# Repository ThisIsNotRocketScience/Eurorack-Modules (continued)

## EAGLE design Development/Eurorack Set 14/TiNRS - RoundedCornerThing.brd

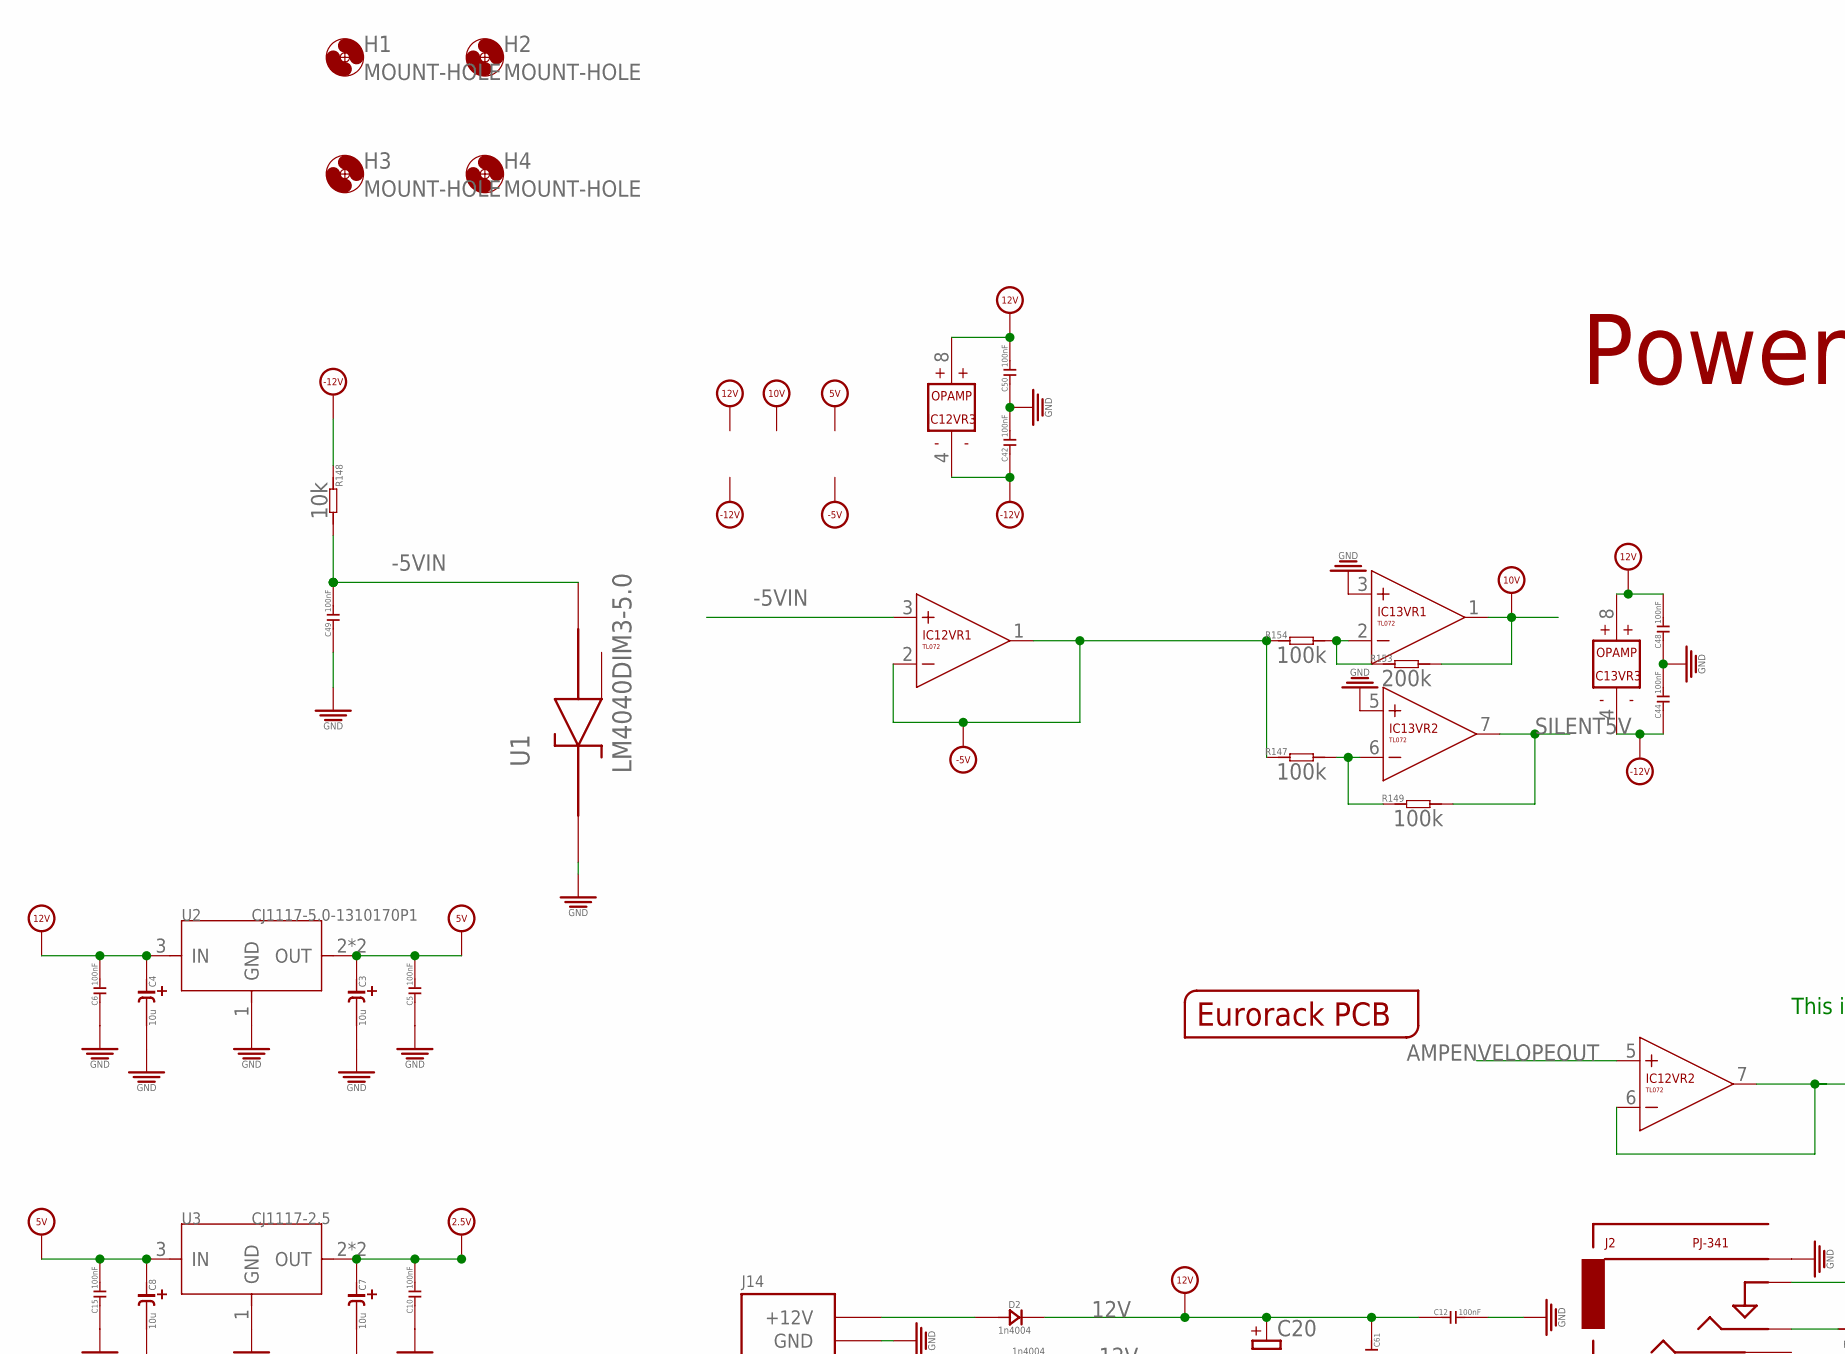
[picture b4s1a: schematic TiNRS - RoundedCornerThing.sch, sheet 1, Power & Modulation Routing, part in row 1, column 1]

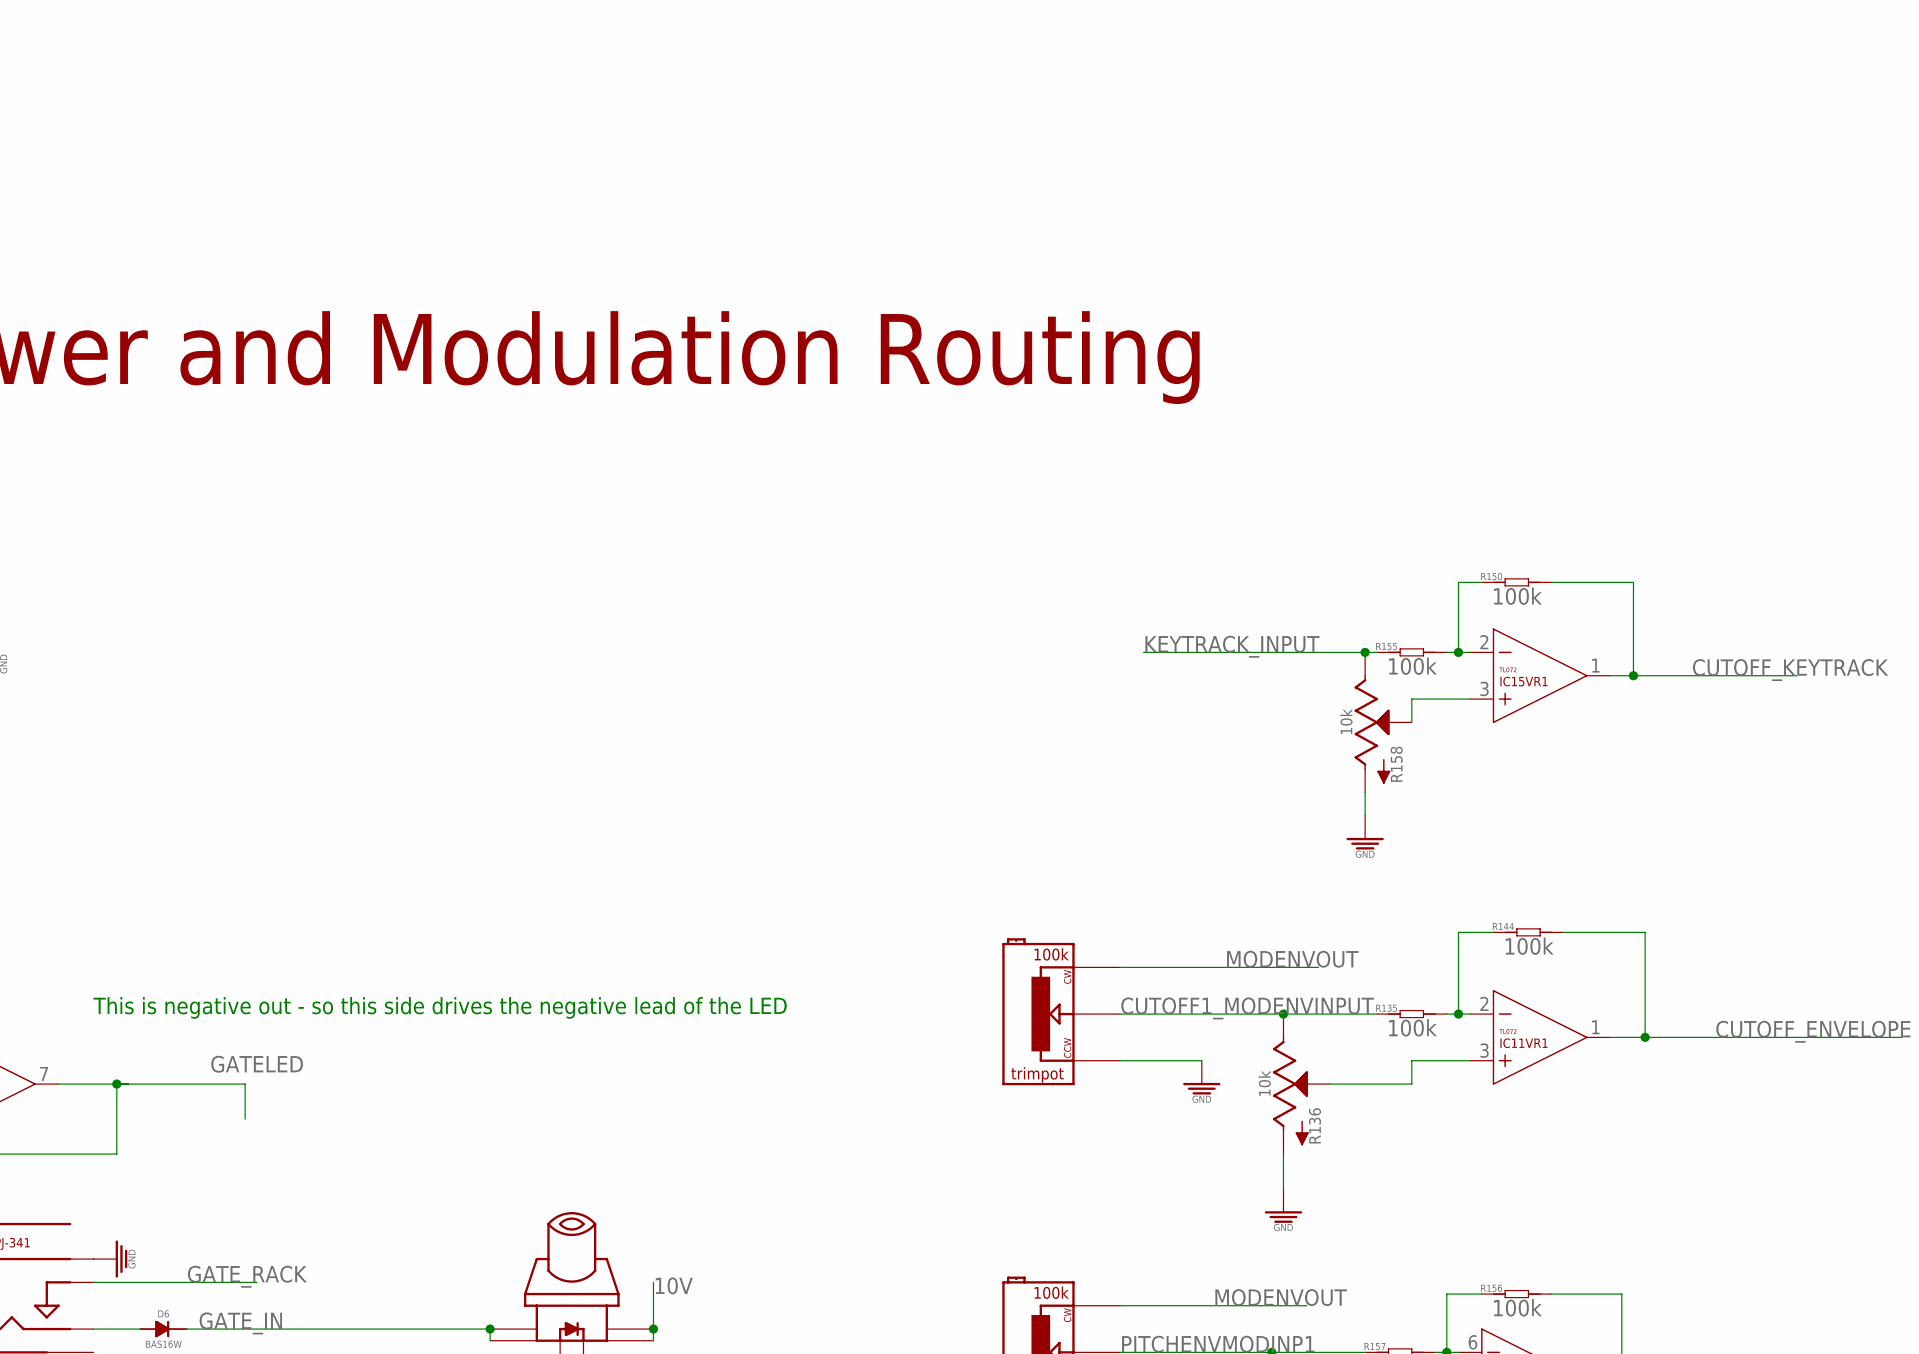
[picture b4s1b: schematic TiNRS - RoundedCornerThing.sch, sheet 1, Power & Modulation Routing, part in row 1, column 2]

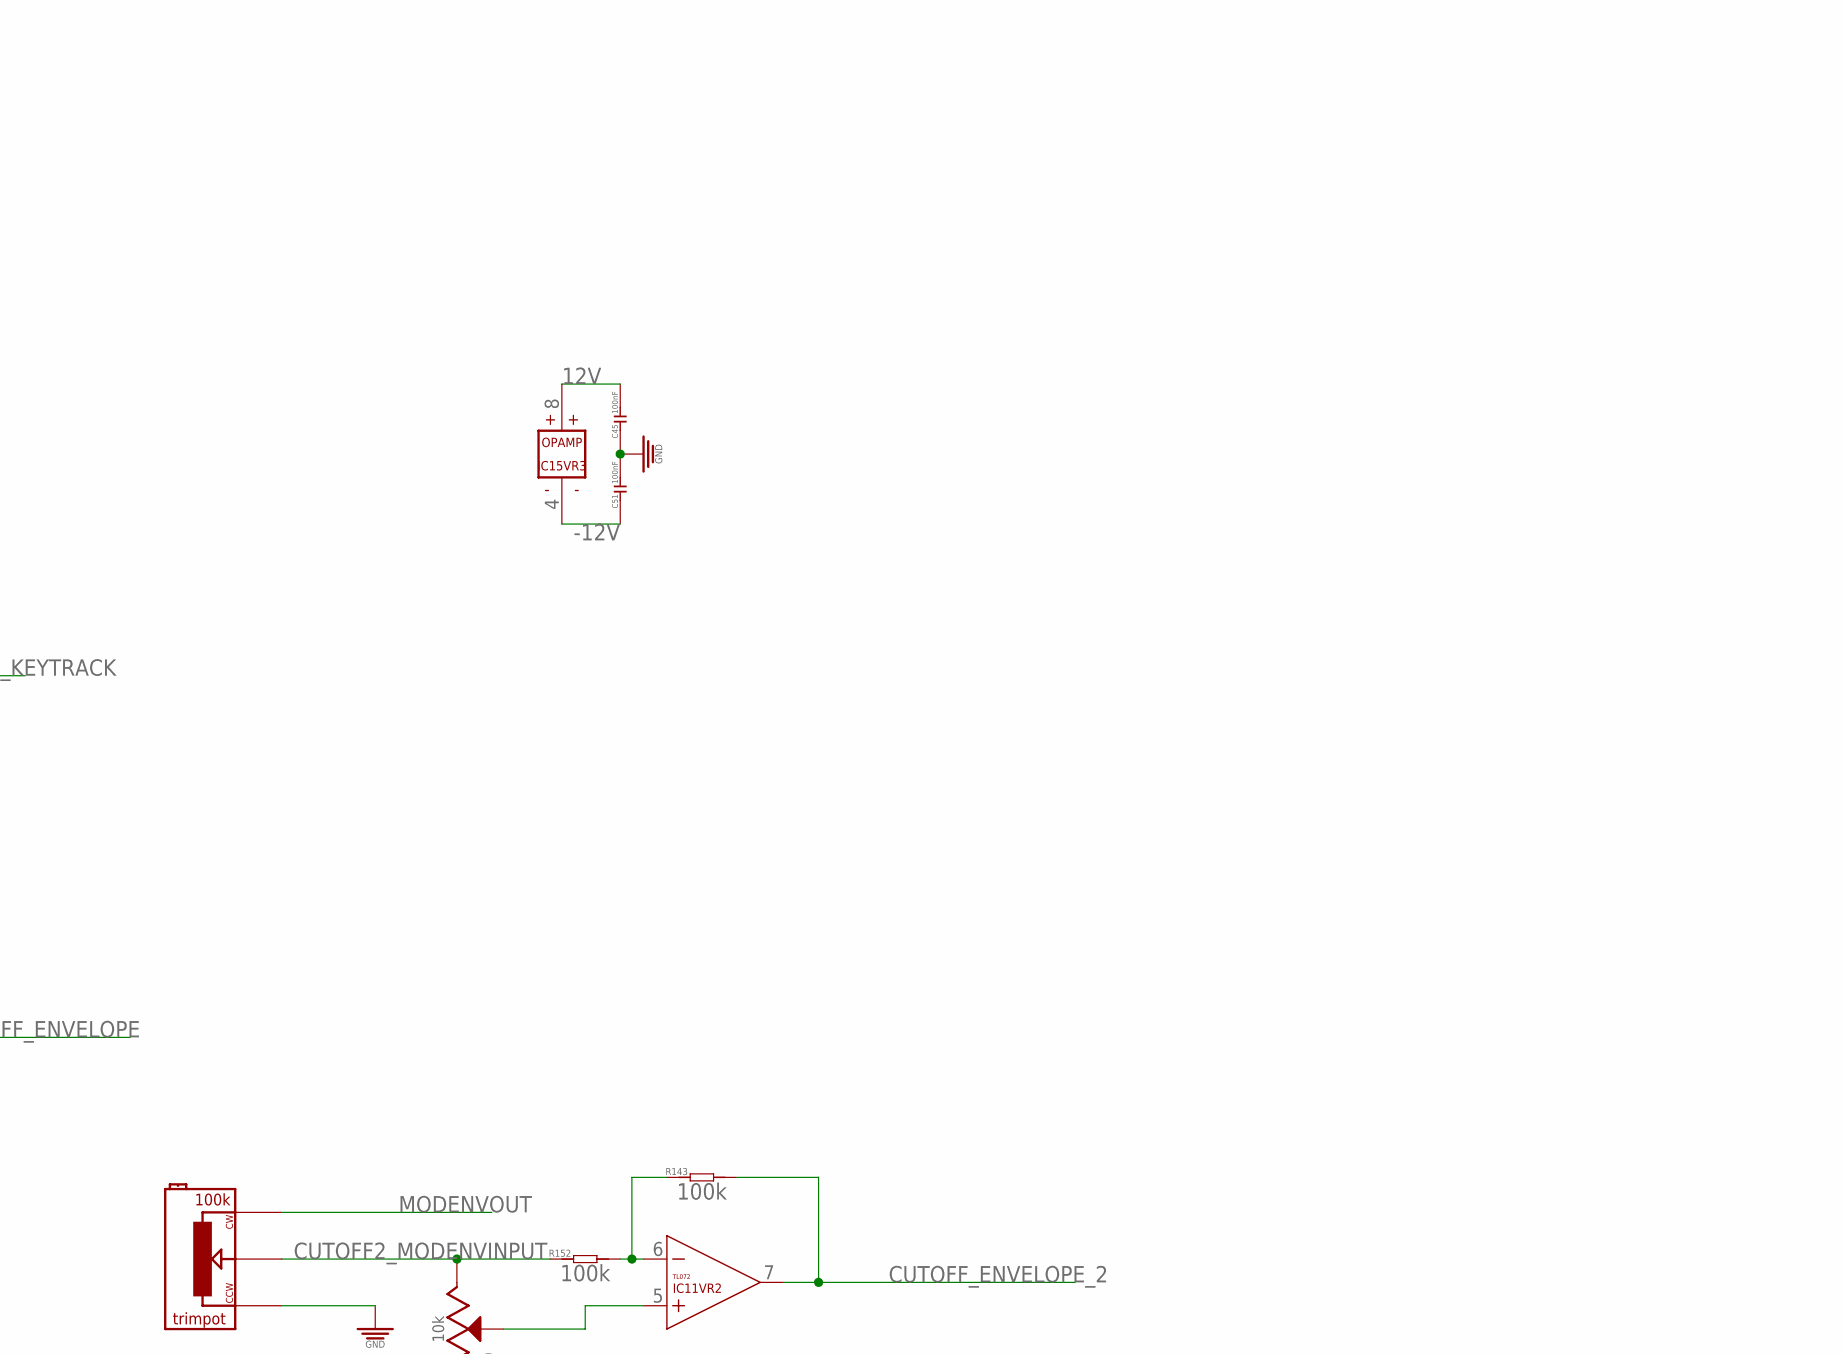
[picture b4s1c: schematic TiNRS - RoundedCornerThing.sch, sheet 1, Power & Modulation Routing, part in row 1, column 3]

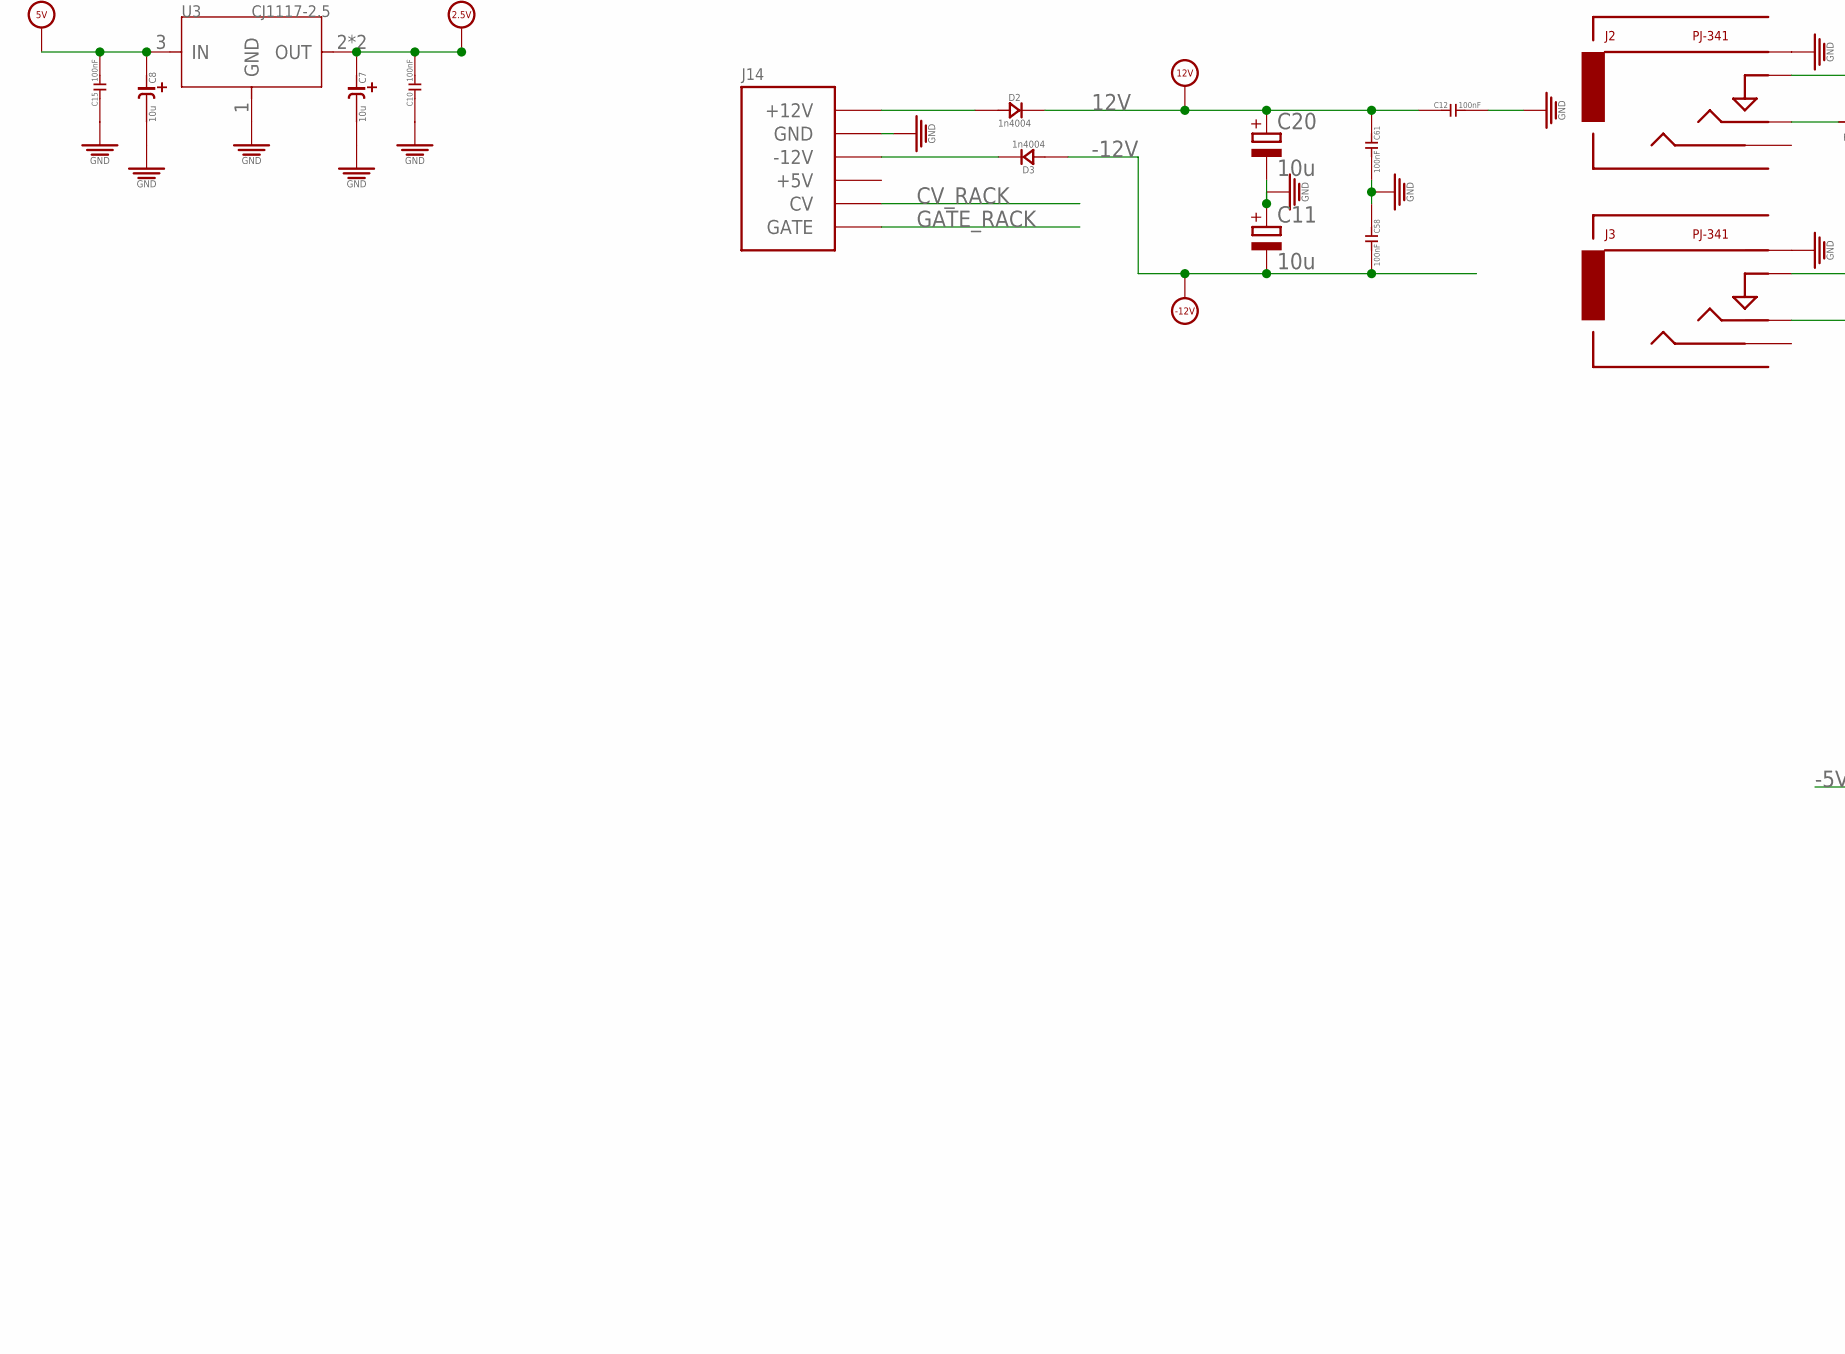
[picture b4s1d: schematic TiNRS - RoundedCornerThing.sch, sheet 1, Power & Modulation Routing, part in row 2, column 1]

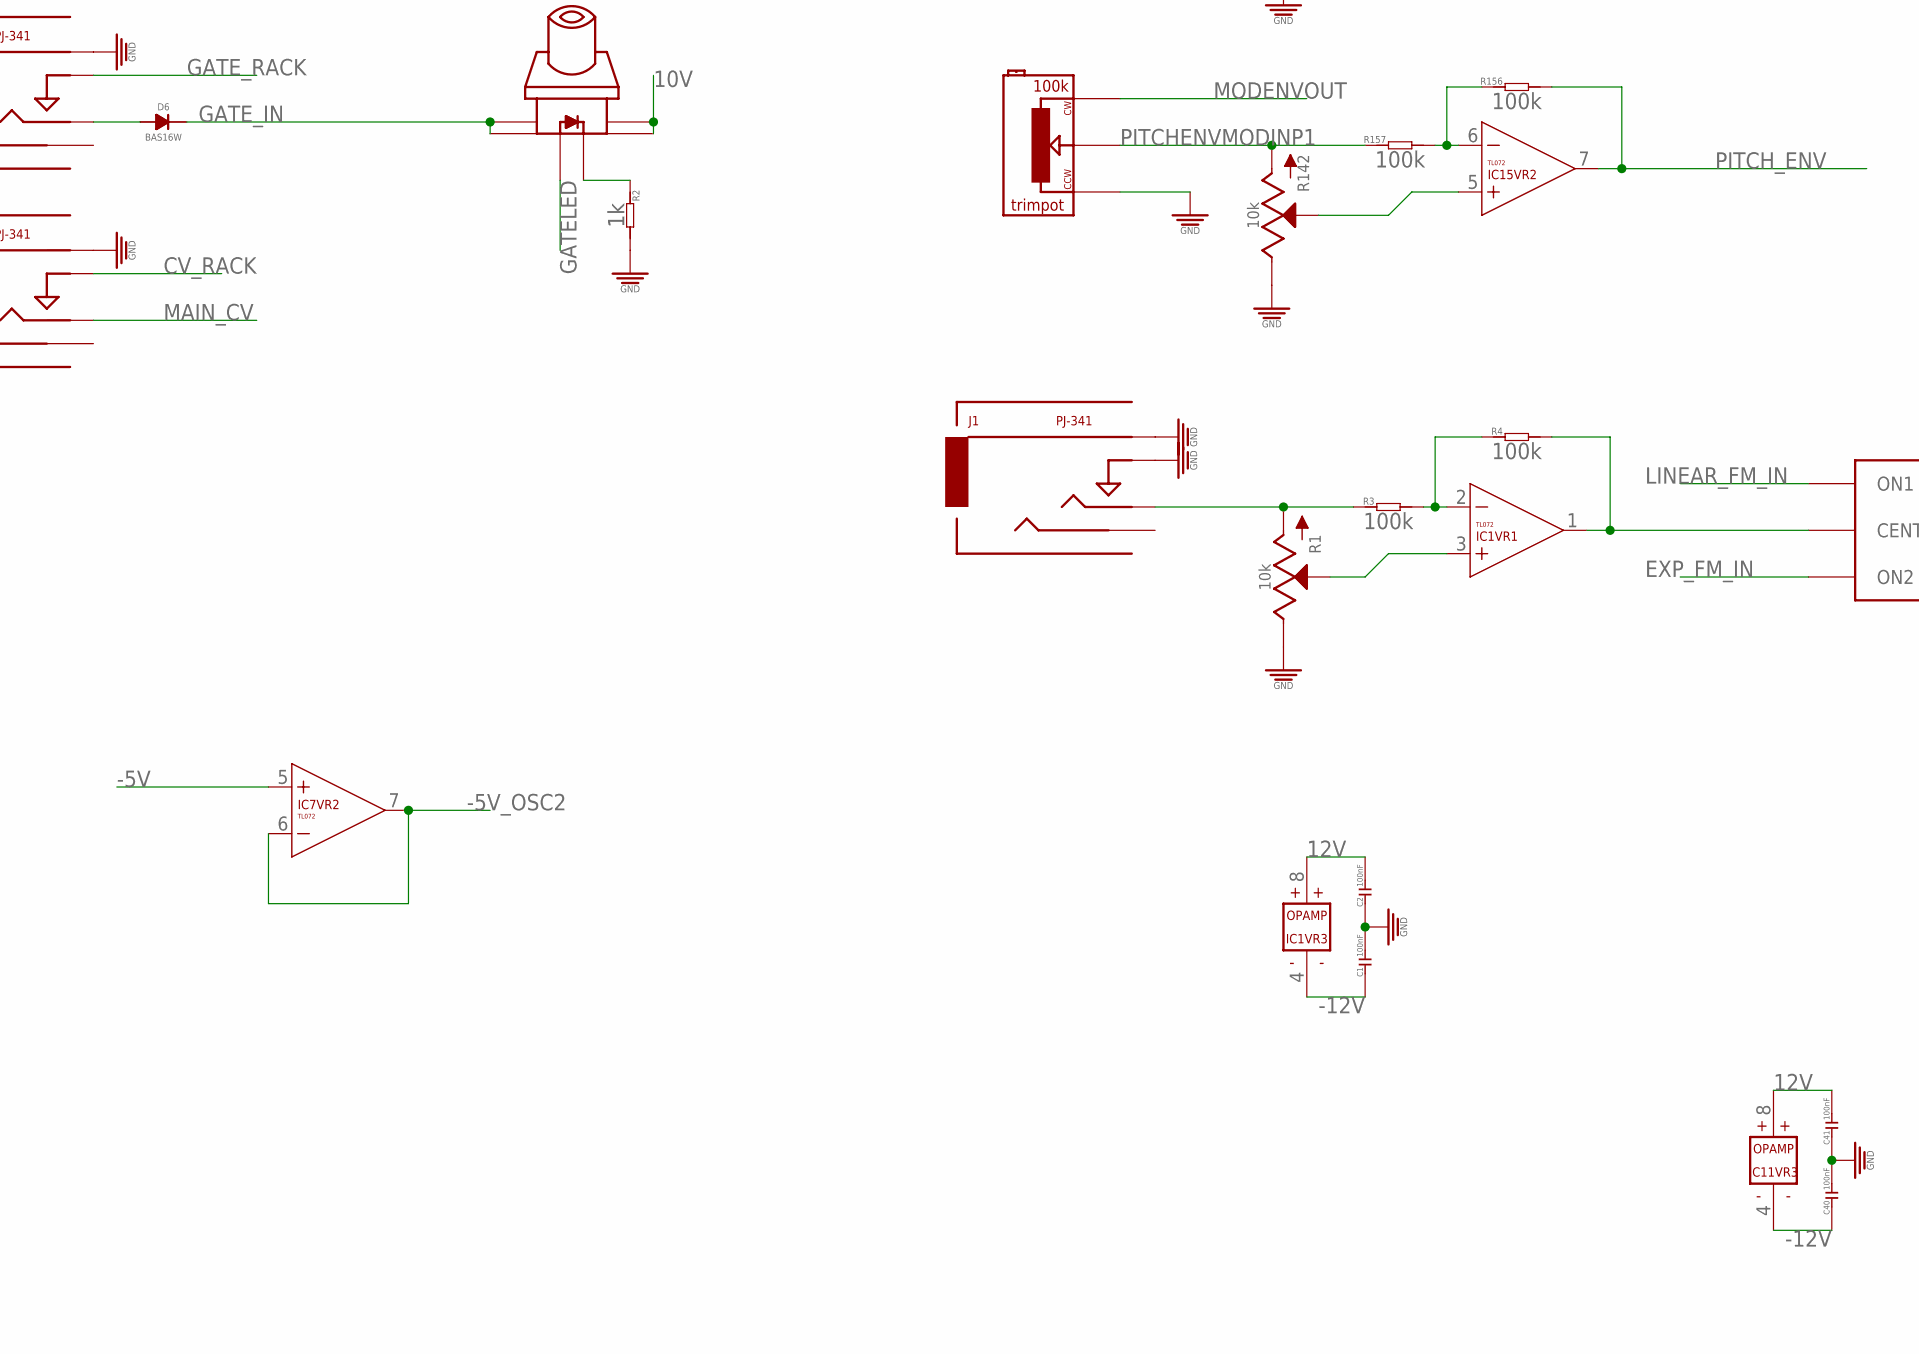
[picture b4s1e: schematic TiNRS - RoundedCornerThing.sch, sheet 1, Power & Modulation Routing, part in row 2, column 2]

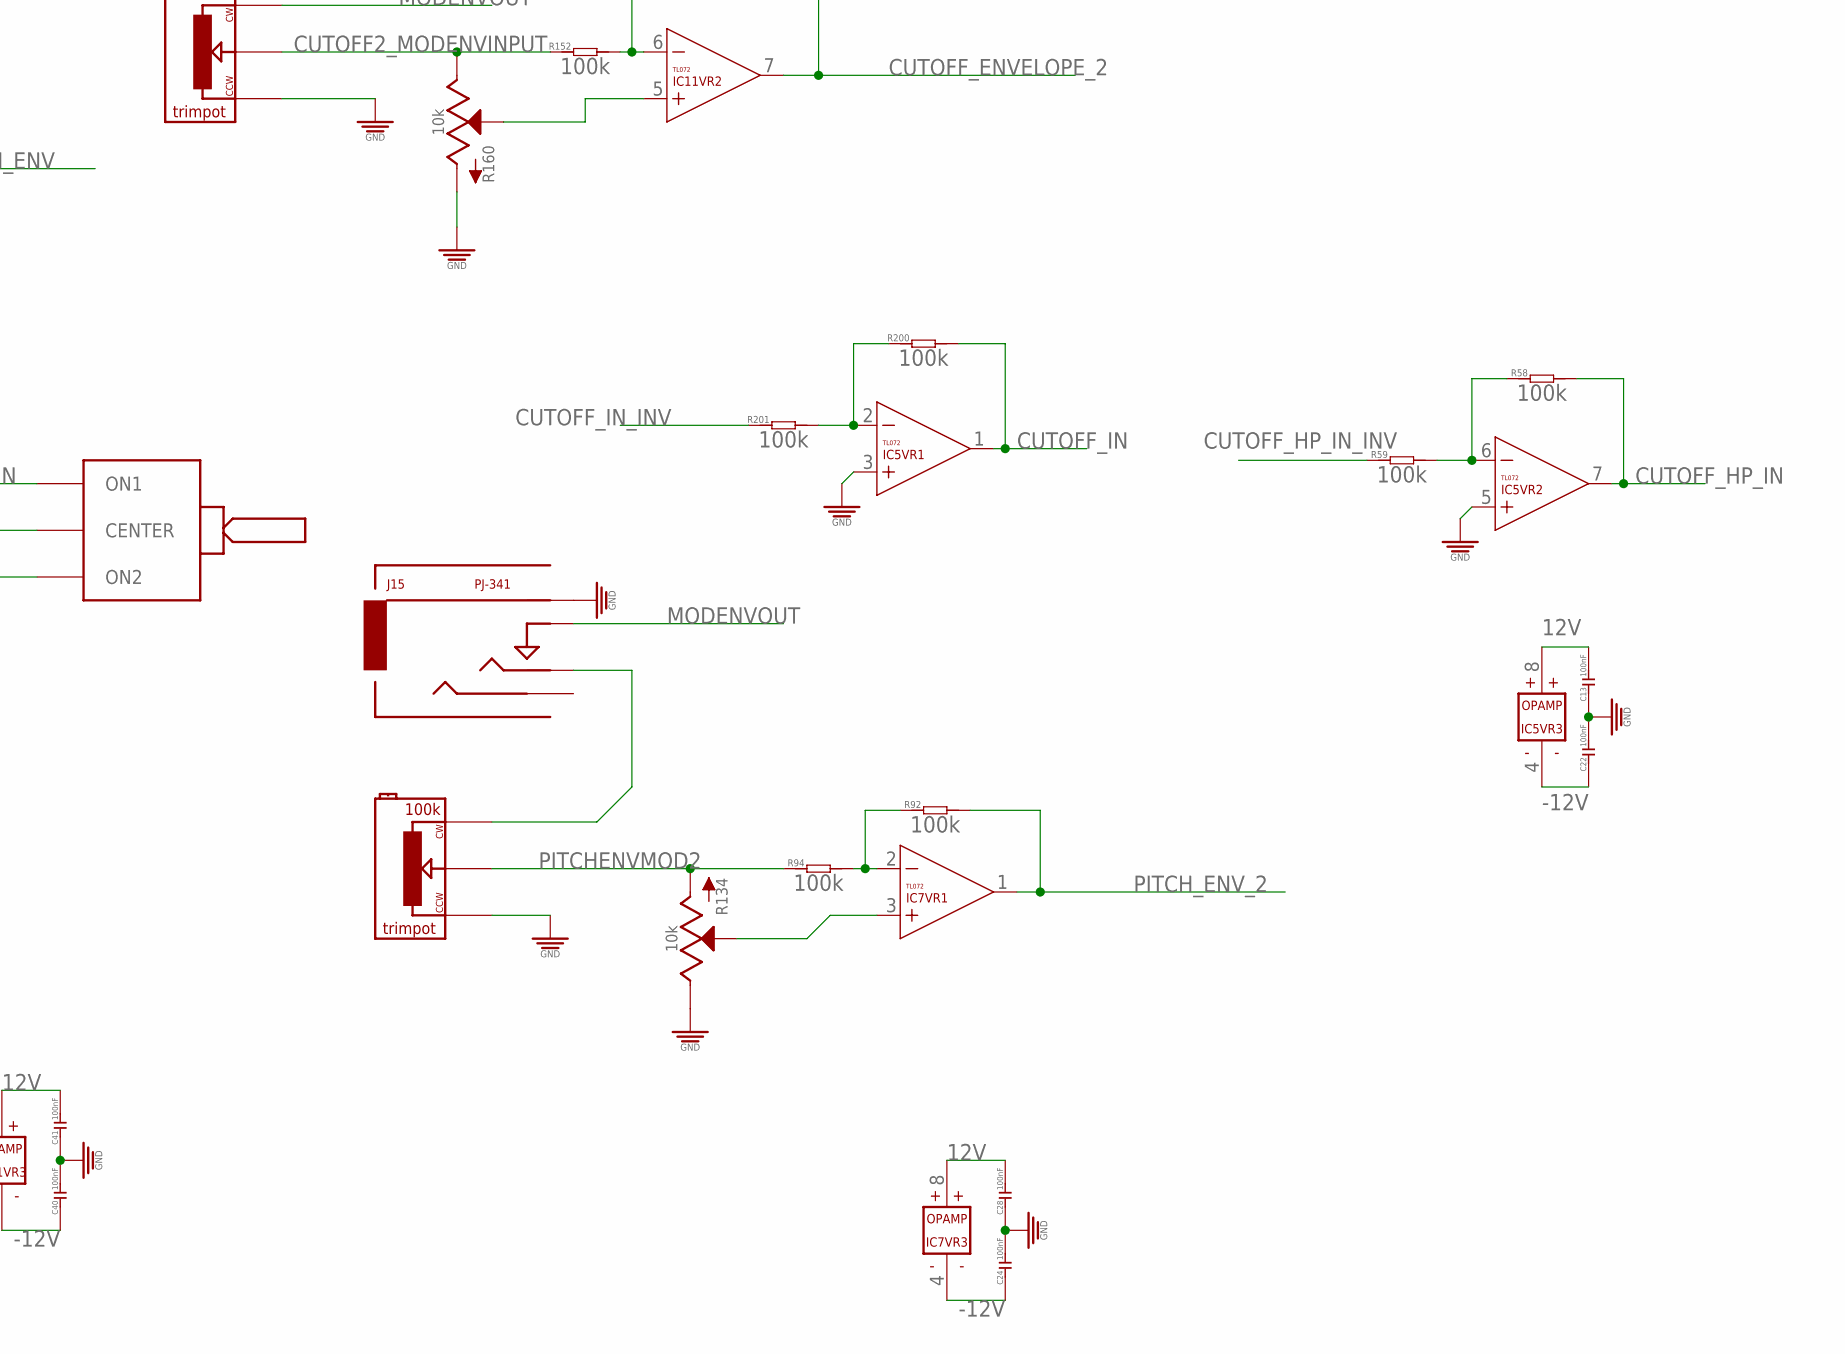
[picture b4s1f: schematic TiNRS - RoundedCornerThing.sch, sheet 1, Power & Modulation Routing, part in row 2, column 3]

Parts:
C1, C2, C12, C13, C22, C24, C28, C40, C41, C42, C44, C45, C48, C50, C51, C58, C61: 100nF; C0603
C3, C4, C7, C8: 10u; CASE-A_3216
C5, C6, C10, C15, C49: 100nF; C0603; MPN 06035C104KAT2A
C11, C20: 10u; CASE_B
D2, D3: 1n4004; DO-214AC
D6: BAS16W; SOT-323
H1, H2, H3, H4: MOUNT-HOLE; 3.2-NOMARKINGS-SMALLSAFEZONE
IC1, IC5, IC7, IC11, IC12, IC13, IC15: TL072; SO08
J1, J2, J3, J15: PJ-341; 3.5MM-JACK-SWITCH-13MM-NOHOLES
J14: POWERSHROUDED; POWER_16_SHROUDED
PCB1: EURORACK_PCB36HP_10CM; EURORACK36HP
R1, R134, R136, R142, R158, R160: 10k; ALPS_POT_SQUAREHOLES
R2: 1k; R0603
R3, R4, R58, R59, R92, R94, R135, R143, R144, R147, R149, R150, R152, R154, R155, R156, R157, R200, R201: 100k; R0603
R148: 10k; R0603
R153: 200k; R0603
R191, R192, R193, R194: 100k; TRIMPOT
S1: ONOFFONNOHOLES; MULTICOMP1MS-ONOFFON_NOHOLES
S2: SWITCH_W_LED_PB6149L-X-102YELLOW; PB6149L
U1: LM4040DIM3-5.0; SOT95P237X112-3N
U2: CJ1117-5.0-1310170P1; SOT223
U3: CJ1117-2.5; SOT223

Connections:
2.5V: C7.+ (1), C10.2, U3.2 (OUT), U3.TER (OUT); also elsewhere on the board
5V: C3.+ (1), C5.2, C8.+ (1), C15.2, U2.2 (OUT), U2.TER (OUT), U3.3 (IN); also elsewhere on the board
10V: IC13.1 (OUT), R153.2, S2.3, S2.4; also elsewhere on the board
12V: C2.2, C4.+ (1), C6.2, C12.1, C13.2, C20.+, C28.2, C41.2, C45.2, C48.2, C50.2, C61.1, D2.2 (-), IC1.8 (V+), IC5.8 (V+), IC7.8 (V+), IC11.8 (V+), IC12.8 (V+), IC13.8 (V+), IC15.8 (V+), U2.3 (IN); also elsewhere on the board
-5V: IC7.5 (+IN), IC12.1 (OUT), IC12.2 (-IN), R147.1, R154.1; also elsewhere on the board
-5VIN: C49.2, IC12.3 (+IN), R148.2, U1.2 (ANODE)
-5V_OSC2: IC7.6 (-IN), IC7.7 (OUT)
-5V_TO_5V: IC13.6 (-IN), R147.2, R149.1
-5_TO_10V: IC13.2 (-IN), R153.1, R154.2
-12V: C1.1, C11.-, C22.1, C24.1, C40.1, C42.1, C44.1, C51.1, C58.2, D3.1 (+), IC1.4 (V-), IC5.4 (V-), IC7.4 (V-), IC11.4 (V-), IC12.4 (V-), IC13.4 (V-), IC15.4 (V-), R148.1; also elsewhere on the board
AMPENVELOPEOUT: IC12.5 (+IN); also elsewhere on the board
CUTOFF1_MODENVINPUT: R135.1, R136.P$1 (E), R192.P$2
CUTOFF2_MODENVINPUT: R152.1, R160.P$1 (E), R194.P$2
CUTOFF_ENVELOPE: IC11.1 (OUT), R144.2
CUTOFF_ENVELOPE_2: IC11.7 (OUT), R143.2
CUTOFF_HP_IN: IC5.7 (OUT), R58.2
CUTOFF_HP_IN_INV: R59.1; also elsewhere on the board
CUTOFF_IN: IC5.1 (OUT), R200.2
CUTOFF_IN_INV: R201.1; also elsewhere on the board
CUTOFF_KEYTRACK: IC15.1 (OUT), R150.2
CV_RACK: J3.SWITCH_B@1 (SWITCH), J3.SWITCH_T@3 (SWITCH), J14.13 (CV), J14.14 (CV)
EXP_FM_IN: S1.3_B (ON2), S1.3_T (ON2); also elsewhere on the board
GATELED: IC12.6 (-IN), IC12.7 (OUT), S2.LEDPOS (POS)
GATE_IN: D6.CATHODE, S2.1, S2.2; also elsewhere on the board
GATE_RACK: J2.SWITCH_B@1 (SWITCH), J2.SWITCH_T@3 (SWITCH), J14.15 (GATE), J14.16 (GATE)
GND: C1.2, C2.1, C3.- (2), C4.- (2), C5.1, C6.1, C7.- (2), C8.- (2), C10.1, C11.+, C12.2, C13.1, C15.1, C20.-, C22.2, C24.2, C28.1, C40.2, C41.1, C42.2, C44.2, C45.1, C48.1, C49.1, C50.1, C51.2, C58.1, C61.2, IC5.3 (+IN), IC5.5 (+IN), IC13.3 (+IN), IC13.5 (+IN), J1.RING_B@1 (RING), J1.RING_T@3 (RING), J1.SWITCH_B@1 (SWITCH), J1.SWITCH_T@3 (SWITCH), J2.RING_B@1 (RING), J2.RING_T@3 (RING), J3.RING_B@1 (RING), J3.RING_T@3 (RING), J14.3 (GND), J14.4 (GND), J14.5 (GND), J14.6 (GND), J14.7 (GND), J14.8 (GND), J15.RING_B@1 (RING), J15.RING_T@3 (RING), R1.P$1 (E), R2.2, R134.P$1 (E), R136.P$3 (A), R142.P$1 (E), R158.P$3 (A), R160.P$3 (A), R191.P$1, R192.P$1, R193.P$1, R194.P$1, U1.1 (CATHODE), U2.1 (GND), U3.1 (GND); also elsewhere on the board
KEYTRACK_INPUT: R155.1, R158.P$1 (E); also elsewhere on the board
LINEAR_FM_IN: S1.1_B (ON1), S1.1_T (ON1)
MAIN_CV: J3.TIP_B@1 (TIP), J3.TIP_T@3 (TIP); also elsewhere on the board
MODENVOUT: J15.SWITCH_B@1 (SWITCH), J15.SWITCH_T@3 (SWITCH), R192.P$3, R193.P$3, R194.P$3; also elsewhere on the board
unnamed: D2.1 (+), J14.9 (+12V), J14.10 (+12V)
unnamed: D3.2 (-), J14.1 (-12V), J14.2 (-12V)
unnamed: R2.1, S2.LEDNEG (NEG)
unnamed: J15.TIP_B@1 (TIP), J15.TIP_T@3 (TIP), R191.P$3
unnamed: IC1.1 (OUT), R4.2, S1.2_B (CENTER), S1.2_T (CENTER)
unnamed: IC5.6 (-IN), R58.1, R59.2
unnamed: IC1.2 (-IN), R3.2, R4.1
unnamed: IC15.2 (-IN), R150.1, R155.2
unnamed: IC15.3 (+IN), R158.P$2 (S)
unnamed: IC11.2 (-IN), R135.2, R144.1
unnamed: IC15.6 (-IN), R156.1, R157.2
unnamed: IC11.3 (+IN), R136.P$2 (S)
unnamed: IC7.2 (-IN), R92.1, R94.2
unnamed: IC7.3 (+IN), R134.P$2 (S)
unnamed: IC15.5 (+IN), R142.P$2 (S)
unnamed: IC1.3 (+IN), R1.P$2 (S)
unnamed: J1.TIP_B@1 (TIP), J1.TIP_T@3 (TIP), R1.P$3 (A), R3.1
unnamed: D6.ANODE, J2.TIP_B@1 (TIP), J2.TIP_T@3 (TIP)
unnamed: IC11.6 (-IN), R143.1, R152.2
unnamed: IC11.5 (+IN), R160.P$2 (S)
unnamed: IC5.2 (-IN), R200.1, R201.2
PITCHENVMOD2: R94.1, R134.P$3 (A), R191.P$2
PITCHENVMODINP1: R142.P$3 (A), R157.1, R193.P$2
PITCH_ENV: IC15.7 (OUT), R156.2
PITCH_ENV_2: IC7.1 (OUT), R92.2
SILENT5V: IC13.7 (OUT), R149.2

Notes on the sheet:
This is negative out - so this side drives the negative lead of the LED
Power and Modulation Routing
